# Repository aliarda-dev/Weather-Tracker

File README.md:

***Weather Tracker***

DHT11 sensöründen okunan sıcaklık ve nem verilerini 16x2 LCD ekranda gösteren basit bir hava durumu takip sistemi geliştirdim. Amacım sensörden veri okuyup LCD ekran üzerinde gösterebilmekti.

***Donanım***

* Arduino Uno
* DHT11 (sıcaklık ve nem sensörü)
* 16x2 LCD Ekran
* 10K Potansiyometre (lcd ekran parlaklık ayarı için)
* 1x330R Direnç

***Nasıl Çalışır?***

* DHT11 sensöründen sıcaklık ve nem değerleri okunur
* Okunan değerler hava_durum() fonksiyonu ile pointer üzerinden ana döngüdeki değişkenlere aktarılır
* Değerler lcd ekranda gösterilir

***Teknik Notlar***

LCD ekran clear() ile silinince ekranda titreme yapıyordu bende sadece değişken karakterleri güncelleyerek kodu güncelledim 

***Geliştirme Fikirleri***

* ESP ile uzaktan takip
* Saatlik veya günlük olarak alınan sıcaklık dataları tutulabilir

***Not***

Projenin pcb dosyaları yüklendi. Bu projede Kicadde footprintinde 3D step dosyası olmayan malzemelere internetten 3D model yüklemeyi öğrendim.

🎥 Proje Demo

📷 Proje PCB Medyası

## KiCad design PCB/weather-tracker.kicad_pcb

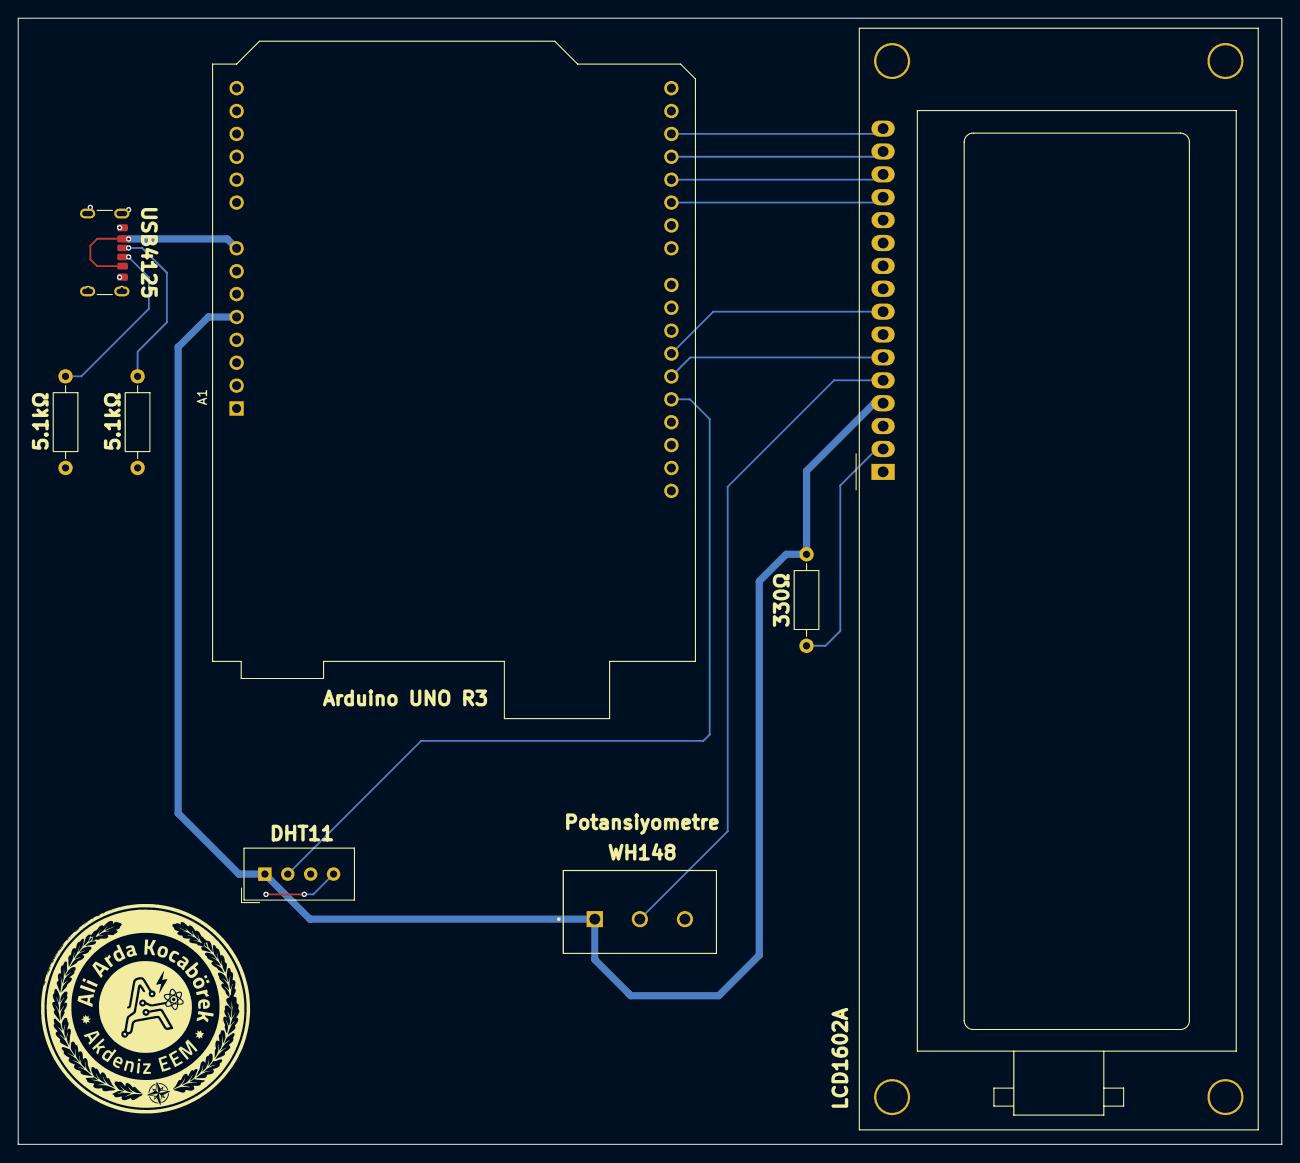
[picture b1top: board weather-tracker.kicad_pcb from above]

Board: 2 copper layers, 140.2 x 125.0 mm, 8 parts (0 on the bottom side), 14 nets.

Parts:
5.1kΩ, 5.1kΩ#2: 5.1kΩ; R_Axial_DIN0207_L6.3mm_D2.5mm_P10.16mm_Horizontal
330Ω: 330Ω; R_Axial_DIN0207_L6.3mm_D2.5mm_P10.16mm_Horizontal
A1: Arduino UNO R3; Arduino_UNO_R3
DHT11: DHT11; Aosong_DHT11_5.5x12.0_P2.54mm
LCD1602A: HY1602E
Potansiyometre: R_Potentiometer_Trim; wh148
USB4125: USB_C_Receptacle_PowerOnly_6P; USB_C_Receptacle_GCT_USB4125-xx-x_6P_TopMnt_Horizontal

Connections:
2: A1.17 (D2), LCD1602A.16 (DB7)
3: A1.18 (D3), LCD1602A.15 (DB6)
4: A1.19 (D4), LCD1602A.14 (DB5)
5: A1.20 (D5), LCD1602A.13 (DB4)
5V: 330Ω.2, A1.5 (+5V), DHT11.1 (VDD), LCD1602A.4 (VDD), Potansiyometre.1
11: A1.26 (D11), LCD1602A.8 (E)
12: A1.27 (D12), LCD1602A.6 (RS)
13: A1.28 (D13), DHT11.2 (DATA)
/IO/V0: LCD1602A.5 (Vo), Potansiyometre.2
GND: 5.1kΩ.2, 5.1kΩ#2.2, A1.6 (GND), A1.7 (GND), A1.29 (GND), DHT11.4 (GND), LCD1602A.1 (LEDK), LCD1602A.3 (VSS), LCD1602A.7 (R/~W), Potansiyometre.3, USB4125.A12 (GND), USB4125.B12 (GND), USB4125.SH (SHIELD)
unnamed: 330Ω.1, LCD1602A.2 (LEDA)
unnamed: 5.1kΩ.1, USB4125.A5 (CC1)
unnamed: 5.1kΩ#2.1, USB4125.B5 (CC2)
VIN: A1.8 (VIN), USB4125.A9 (VBUS), USB4125.B9 (VBUS)
